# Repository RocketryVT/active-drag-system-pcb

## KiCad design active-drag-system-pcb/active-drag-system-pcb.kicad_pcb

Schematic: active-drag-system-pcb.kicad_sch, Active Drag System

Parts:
C1, C5: 0.1uF; C_0201_0603Metric_Pad0.64x0.40mm_HandSolder; Max Voltage 16 V; Tolerance 10%
C2, C3, C11, C12: 10uF; C_0805_2012Metric_Pad1.18x1.45mm_HandSolder; Max Voltage 16V; Tolerance 10%
C4: 1uF; C_0402_1005Metric_Pad0.74x0.62mm_HandSolder; Max Voltage 6.3V; Tolerance 20%
C6: 22p; C_0201_0603Metric; Max Voltage 25V; Tolerance 5%
C7, C8, C9, C10: 22uF; C_0402_1005Metric_Pad0.74x0.62mm_HandSolder; Max Voltage 10V; Tolerance 20%
C13, C16, C17, C18: 2.2u; C_0402_1005Metric_Pad0.74x0.62mm_HandSolder; Max Voltage 6.3V; Tolerance 20%
C14, C15, C19, C20, C21, C22, C23, C24, C27, C47, C48, C49, C50, C51, C53, C55, C56: 100n; C_0201_0603Metric_Pad0.64x0.40mm_HandSolder; Max Voltage 6.3V; Tolerance 10%
C25, C26: 15p; C_0201_0603Metric; Max Voltage 25V; Tolerance 5%
C46: 1000pF; C_0402_1005Metric_Pad0.74x0.62mm_HandSolder; Max Voltage 6.3V; Tolerance 10%
C52: 10n; C_0201_0603Metric_Pad0.64x0.40mm_HandSolder; Max Voltage 6.3V; Tolerance 10%
C54: 2.2u; C_0402_1005Metric_Pad0.74x0.62mm_HandSolder; Max Voltage 6.3V; Tolerance 10%
D7: WL-SMCW_0603
H1, H2, H3, H4: MountingHole; MountingHole_2.7mm_M2.5
IC1: ADC1283IPT; SOP65P640X120-16N; Manufacturer_Part_Number ADC1283IPT; Mouser Part Number 511-ADC1283IPT
J1: USB_B_Micro; USB_Micro-B_Amphenol_10103594-0001LF_Horizontal
L1: 104CDMCCDS-1R5MC; IND_-1R5MC_SUM
Q7: DMG1012T; SOT-523
R1, R2, R3: 100k; R_0402_1005Metric_Pad0.72x0.64mm_HandSolder; Tolerance 0.1%
R4: 200k; R_0402_1005Metric_Pad0.72x0.64mm_HandSolder; Tolerance 1%
R5: 150k; R_0402_1005Metric_Pad0.72x0.64mm_HandSolder; Tolerance 0.1%
R6, R8: 100k; R_0402_1005Metric_Pad0.72x0.64mm_HandSolder; Tolerance 1%
R7: 20k; R_0402_1005Metric_Pad0.72x0.64mm_HandSolder; Tolerance 0.1%
R9: 100; R_0402_1005Metric_Pad0.72x0.64mm_HandSolder; Tolerance 1%
R28, R29: 27; R_0201_0603Metric_Pad0.64x0.40mm_HandSolder; Tolerance 1%
R30: 1; R_0402_1005Metric_Pad0.72x0.64mm_HandSolder; Tolerance 1%
R31: 200; R_0603_1608Metric_Pad0.98x0.95mm_HandSolder; Tolerance 1%
R32, R33: 1k; R_0402_1005Metric_Pad0.72x0.64mm_HandSolder; Tolerance 1%
R34, R35: 10k; R_0402_1005Metric_Pad0.72x0.64mm_HandSolder; Tolerance 1%
SW1: PTS815 SJM 250 SMTR LFS; SW4_PTS815 SJM 250 SMTR LFS_CNK
U1: TPS51386RJNR; VREG_TPS51386RJNR; PARTREV *
U2: LD39200PU33R; SON_DFN6_3X3_STM
U3, U4: PMEG3050EP_115; SODFL4725X110N
U5: RP2040; QFN-56-1EP_7x7mm_P0.4mm_EP3.2x3.2mm
U6: W25Q128JVS; SOIC-8_5.23x5.23mm_P1.27mm
U13: MS5611-01BA; LGA-8_3x5mm_P1.25mm
U14: LSM6DSV16XTR; LGA14L_LSM6_STM
U15: ADXL375BCCZ; LGA_CC-14-1_ADI
U16: IIM-42653; PQFN50P250X300X97-14N; PARTREV 1.1
X1: ABM8-272-T3; ABM8-272-T3_ABR

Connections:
+1V1: C15.1, C17.1, C22.1, U5.23 (DVDD), U5.45 (VREG_VOUT), U5.50 (DVDD)
+3V3: C12.1, C13.1, C14.1, C16.1, C19.1, C20.1, C21.1, C23.1, C24.1, C27.1, C47.1, C48.1, C49.1, C50.1, C51.1, C52.1, C53.1, C54.1, C55.1, C56.1, IC1.2 (AVCC), IC1.13 (DVCC), Q7.1 (G), R31.1, R34.1, R35.1, U2.1 (OUT), U2.2 (ADJ/SENSE), U5.1 (IOVDD), U5.10 (IOVDD), U5.22 (IOVDD), U5.33 (IOVDD), U5.42 (IOVDD), U5.44 (VREG_IN), U5.48 (USB_VDD), U5.49 (IOVDD), U6.8 (VCC), U13.1 (VDD), U13.2 (PS), U14.5 (VDD_IO), U14.8 (VDD), U14.12 (CS), U15.1 (VDD_I/O), U15.6 (VS), U15.7 (*CS), U15.12 (SDO/ALT_ADDRESS), U16.5 (VDDIO), U16.8 (VDD), U16.12 (AP_CS); also elsewhere on the board
+5V: C6.2, C7.1, C8.1, C9.1, C10.1, L1.1, R5.2, U4.2 (A)
+BATT: C1.1, C2.1, C3.1, J1.1, R1.1, U1.1 (VIN); also elsewhere on the board
-BATT: C1.2, C2.2, C3.2, C4.2, C7.2, C8.2, C9.2, C10.2, C11.2, C12.2, C13.2, C14.2, C15.2, C16.2, C17.2, C18.2, C19.2, C20.2, C21.2, C22.2, C23.2, C24.2, C25.2, C26.2, C27.2, C46.2, C47.2, C48.2, C49.2, C50.2, C51.2, C52.2, C53.2, C54.2, C55.2, C56.2, D7.1, IC1.3 (AGND), IC1.12 (DGND), J1.2, R2.1, R6.2, R7.1, SW1.3, SW1.4, U1.2 (PGND), U1.10 (AGND), U2.3 (GND), U2.7 (GND), U5.19 (TESTEN), U5.57 (GND), U6.4 (GND), U13.3 (GND), U13.4 (CSB), U13.5 (CSB), U14.1 (SDO/SA0), U14.2 (SDx/AH1/QVAR1), U14.3 (SCx/AH2/QVAR2), U14.6 (GND), U14.7 (GND), U15.2 (GND), U15.3 (RESERVED), U15.4 (GND), U15.5 (GND), U15.11 (RESERVED), U16.1 (AP_SDO/AP_AD0), U16.6 (GND), U16.7 (RESV), X1.2, X1.4; also elsewhere on the board
/ADC_VREF: R30.1, R31.2
/GPIO6: U5.8 (GPIO6)
/GPIO8: U5.11 (GPIO8)
/GPIO10: U5.13 (GPIO10)
/GPIO16: U5.27 (GPIO16)
/GPIO17: U5.28 (GPIO17)
/GPIO22: U5.34 (GPIO22)
/GPIO24: U5.36 (GPIO24)
/GPIO25: R9.1, U5.37 (GPIO25)
/GPIO26_ADC0: U5.38 (GPIO26_ADC0)
/GPIO27_ADC1: U5.39 (GPIO27_ADC1)
/GPIO28_ADC2: U5.40 (GPIO28_ADC2)
/GPIO29_ADC3: Q7.2 (S), U5.41 (GPIO29_ADC3)
/HALL_A: U5.2 (GPIO0)
/HALL_B: U5.4 (GPIO2)
/HALL_C: U5.6 (GPIO4)
/HIGHG_INT1: U15.8 (INT1)
/HIGHG_INT2: U15.9 (INT2)
/HIN_A: U5.3 (GPIO1)
/HIN_B: U5.5 (GPIO3)
/HIN_C: U5.7 (GPIO5)
/I2C0_SCL: R34.2, U5.32 (GPIO21), U13.8 (SCLK), U14.13 (SCL), U15.14 (SCL/SCLK), U16.13 (AP_SCL/AP_SCLK)
/I2C0_SDA: R35.2, U5.31 (GPIO20), U13.7 (SDI/SDA), U14.14 (SDA), U15.13 (SDA/SDI/SDIO), U16.14 (AP_SDA/AP_SDIO/AP_SDI)
/I2C1_SCL: U5.30 (GPIO19)
/I2C1_SDA: U5.29 (GPIO18)
/LOWG_INT1: U14.4 (INT1), U14.9 (INT2)
/MIDG_INT1: U16.4 (INT1/INT)
/NLIN_A: U5.9 (GPIO7)
/NLIN_B: U5.12 (GPIO9)
/NLIN_C: U5.14 (GPIO11)
/QSPI_SCLK: U5.52 (QSPI_SCLK), U6.6 (CLK)
/QSPI_SD0: U5.53 (QSPI_SD0), U6.5 (DI(IO0))
/QSPI_SD1: U5.55 (QSPI_SD1), U6.2 (DO(IO1))
/QSPI_SD2: U5.54 (QSPI_SD2), U6.3 (IO2)
/QSPI_SD3: U5.51 (QSPI_SD3), U6.7 (IO3)
/QSPI_SS: R33.2, U5.56 (QSPI_SS), U6.1 (~CS)
/RP2040_CLKOUT1: U5.35 (GPIO23), U16.9 (INT2/FSYNC/CLKIN)
/RUN: U5.26 (RUN)
/SPI1_CSn: IC1.1 (~CS), U5.16 (GPIO13)
/SPI1_RX: IC1.15 (DOUT), U5.15 (GPIO12)
/SPI1_SCK: IC1.16 (SCLK), U5.17 (GPIO14)
/SPI1_TX: IC1.14 (DIN), U5.18 (GPIO15)
/SWCLK: U5.24 (SWCLK)
/SWD: U5.25 (SWD)
/USB_D+: R28.1; also elsewhere on the board
/USB_D-: R29.1; also elsewhere on the board
/VSYS: C11.1, R4.1, R8.1, U2.6 (IN), U3.1 (K), U4.1 (K)
/XIN: C26.1, U5.20 (XIN), X1.1
/XOUT: R32.1, U5.21 (XOUT)
CURRENT_SENSE_A: IC1.4 (IN0); also elsewhere on the board
CURRENT_SENSE_B: IC1.6 (IN2); also elsewhere on the board
CURRENT_SENSE_C: IC1.9 (IN5); also elsewhere on the board
unnamed: C25.1, R32.2, X1.3
unnamed: D7.2, R9.2
unnamed: C46.1, Q7.3 (D), R4.2, R6.1
unnamed: R33.1, SW1.1, SW1.2
unnamed: R1.2, R2.2, U1.11 (EN)
unnamed: C6.1, R5.1, R7.2, U1.4 (FB)
unnamed: R3.2, U1.3 (PG)
unnamed: C5.1, L1.2, U1.7 (SW)
unnamed: C5.2, U1.8 (VBST)
unnamed: C4.1, R3.1, U1.9 (VCC)
unnamed: R8.2, U2.5 (EN)
unnamed: C18.1, R30.2, U5.43 (ADC_AVDD)
unnamed: R29.2, U5.46 (USB_DM)
unnamed: R28.2, U5.47 (USB_DP)
VBUS: U3.2 (A); also elsewhere on the board
VOLTAGE_SENSE_A: IC1.5 (IN1); also elsewhere on the board
VOLTAGE_SENSE_B: IC1.7 (IN3); also elsewhere on the board
VOLTAGE_SENSE_C: IC1.10 (IN6); also elsewhere on the board

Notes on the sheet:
Power
Crystal
Motor Control
Sensors
Altimeter
Mid-G IMU
I2C0 Pullups
RP2040 (Primary MCU)
Low-G IMU
High-G IMU
12 MHz
Flash

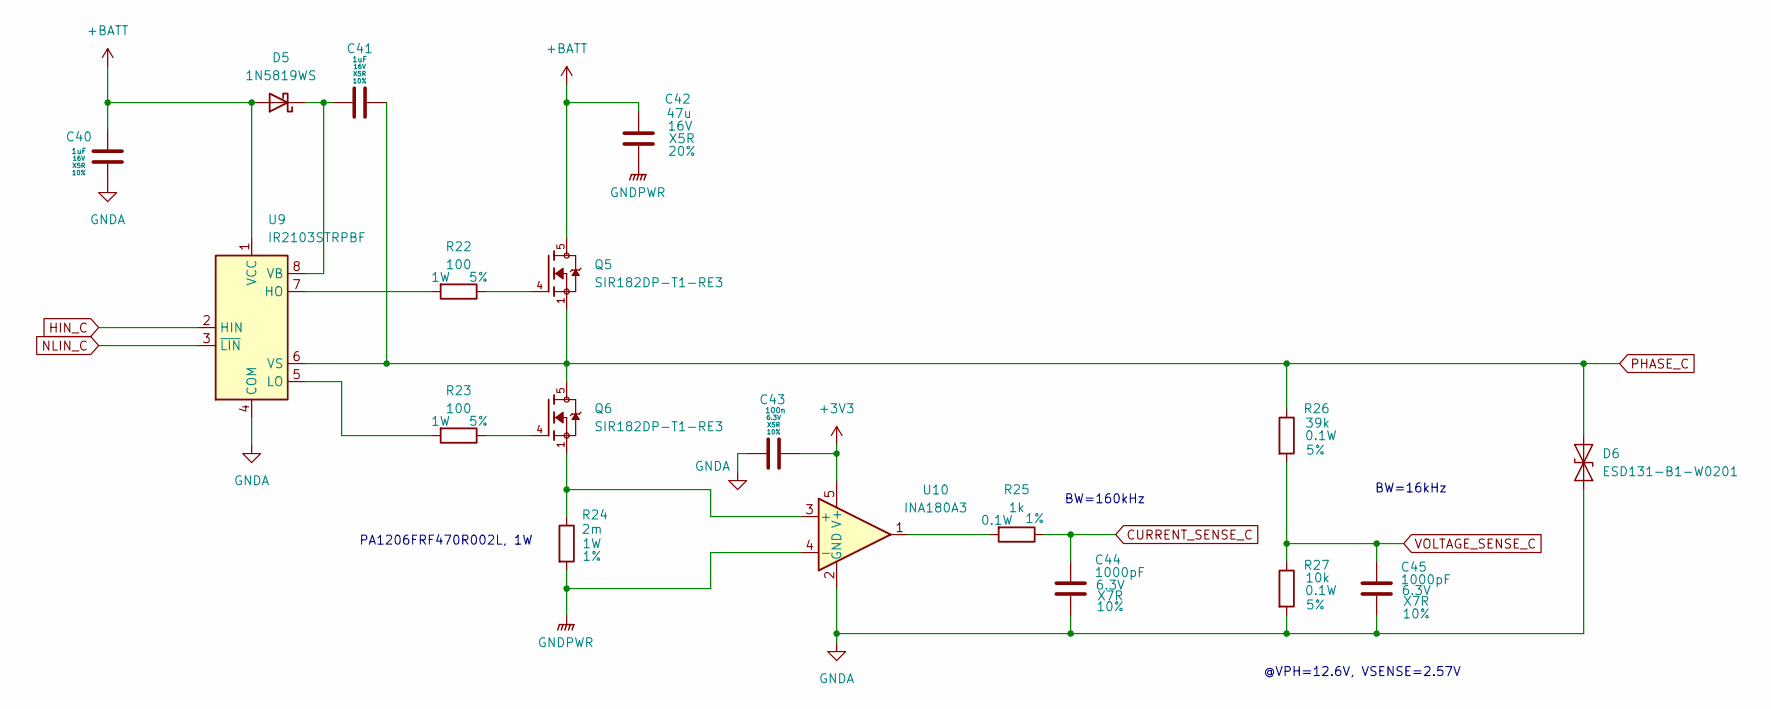
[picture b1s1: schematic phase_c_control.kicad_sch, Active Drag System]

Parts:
C40, C41: 1uF; C_0402_1005Metric_Pad0.74x0.62mm_HandSolder; Max Voltage 16V; Tolerance 10%
C42: 47u; C_1210_3225Metric_Pad1.33x2.70mm_HandSolder; Max Voltage 16V; Tolerance 20%
C43: 100n; C_0201_0603Metric_Pad0.64x0.40mm_HandSolder; Max Voltage 6.3V; Tolerance 10%
C44, C45: 1000pF; C_0402_1005Metric_Pad0.74x0.62mm_HandSolder; Max Voltage 6.3V; Tolerance 10%
D5: 1N5819WS; D_SOD-323
D6: ESD131-B1-W0201; Infineon_SG-WLL-2-3_0.58x0.28_P0.36mm
Q5, Q6: SIR182DP-T1-RE3; TRANS_SIR182DP-T1-RE3; PARTREV B
R22, R23: 100; R_2512_6332Metric_Pad1.40x3.35mm_HandSolder; Tolerance 5%
R24: 2m; R_1206_3216Metric_Pad1.30x1.75mm_HandSolder; Tolerance 1%
R25: 1k; R_0402_1005Metric_Pad0.72x0.64mm_HandSolder; Tolerance 1%
R26: 39k; R_0402_1005Metric_Pad0.72x0.64mm_HandSolder; Tolerance 5%
R27: 10k; R_0402_1005Metric_Pad0.72x0.64mm_HandSolder; Tolerance 5%
U9: IR2103STRPBF; SO8N_INF-L
U10: INA180A3; SOT-23-5

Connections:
+3V3: C43.2, U10.5 (V+); also elsewhere on the board
+BATT: C40.1, C42.1, D5.2 (A), Q5.5, U9.1 (VCC); also elsewhere on the board
-BATT: C40.2, C42.2, C43.1, C44.2, C45.2, D6.1 (A1), R24.2, R27.2, U9.4 (COM), U10.2 (GND), U10.4 (-); also elsewhere on the board
CURRENT_SENSE_C: C44.1, R25.1; also elsewhere on the board
HIN_C: U9.2 (HIN)
NLIN_C: U9.3 (~LIN)
unnamed: C41.2, D5.1 (K), U9.8 (VB)
unnamed: Q5.4, R22.1
unnamed: Q6.4, R23.1
unnamed: R25.2, U10.1
unnamed: R22.2, U9.7 (HO)
unnamed: R23.2, U9.5 (LO)
unnamed: Q6.1, R24.1, U10.3 (+)
PHASE_C: C41.1, D6.2 (A2), Q5.1, Q6.5, R26.1, U9.6 (VS)
VOLTAGE_SENSE_C: C45.1, R26.2, R27.1; also elsewhere on the board

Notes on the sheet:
PA1206FRF470R002L, 1W
BW=16kHz
BW=160kHz
@VPH=12.6V, VSENSE=2.57V

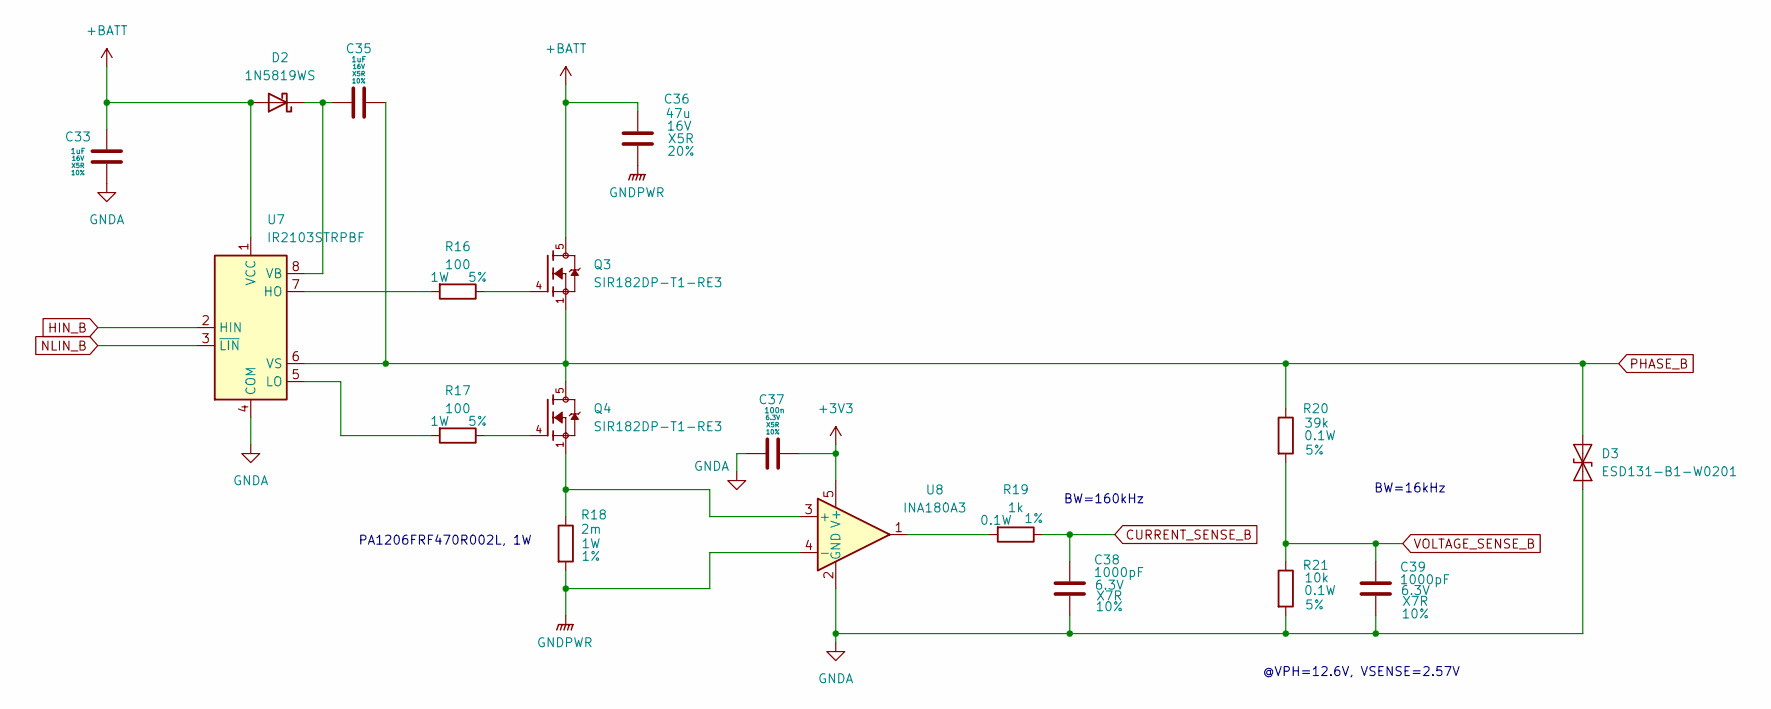
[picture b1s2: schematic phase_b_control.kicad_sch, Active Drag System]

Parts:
C33, C35: 1uF; C_0402_1005Metric_Pad0.74x0.62mm_HandSolder; Max Voltage 16V; Tolerance 10%
C36: 47u; C_1210_3225Metric_Pad1.33x2.70mm_HandSolder; Max Voltage 16V; Tolerance 20%
C37: 100n; C_0201_0603Metric_Pad0.64x0.40mm_HandSolder; Max Voltage 6.3V; Tolerance 10%
C38, C39: 1000pF; C_0402_1005Metric_Pad0.74x0.62mm_HandSolder; Max Voltage 6.3V; Tolerance 10%
D2: 1N5819WS; D_SOD-323
D3: ESD131-B1-W0201; Infineon_SG-WLL-2-3_0.58x0.28_P0.36mm
Q3, Q4: SIR182DP-T1-RE3; TRANS_SIR182DP-T1-RE3; PARTREV B
R16, R17: 100; R_2512_6332Metric_Pad1.40x3.35mm_HandSolder; Tolerance 5%
R18: 2m; R_1206_3216Metric_Pad1.30x1.75mm_HandSolder; Tolerance 1%
R19: 1k; R_0402_1005Metric_Pad0.72x0.64mm_HandSolder; Tolerance 1%
R20: 39k; R_0402_1005Metric_Pad0.72x0.64mm_HandSolder; Tolerance 5%
R21: 10k; R_0402_1005Metric_Pad0.72x0.64mm_HandSolder; Tolerance 5%
U7: IR2103STRPBF; SO8N_INF-L
U8: INA180A3; SOT-23-5

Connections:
+3V3: C37.2, U8.5 (V+); also elsewhere on the board
+BATT: C33.1, C36.1, D2.2 (A), Q3.5, U7.1 (VCC); also elsewhere on the board
-BATT: C33.2, C36.2, C37.1, C38.2, C39.2, D3.1 (A1), R18.2, R21.2, U7.4 (COM), U8.2 (GND), U8.4 (-); also elsewhere on the board
CURRENT_SENSE_B: C38.1, R19.1; also elsewhere on the board
HIN_B: U7.2 (HIN)
NLIN_B: U7.3 (~LIN)
unnamed: C35.2, D2.1 (K), U7.8 (VB)
unnamed: Q3.4, R16.1
unnamed: Q4.4, R17.1
unnamed: R19.2, U8.1
unnamed: R16.2, U7.7 (HO)
unnamed: R17.2, U7.5 (LO)
unnamed: Q4.1, R18.1, U8.3 (+)
PHASE_B: C35.1, D3.2 (A2), Q3.1, Q4.5, R20.1, U7.6 (VS)
VOLTAGE_SENSE_B: C39.1, R20.2, R21.1; also elsewhere on the board

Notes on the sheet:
PA1206FRF470R002L, 1W
BW=16kHz
BW=160kHz
@VPH=12.6V, VSENSE=2.57V

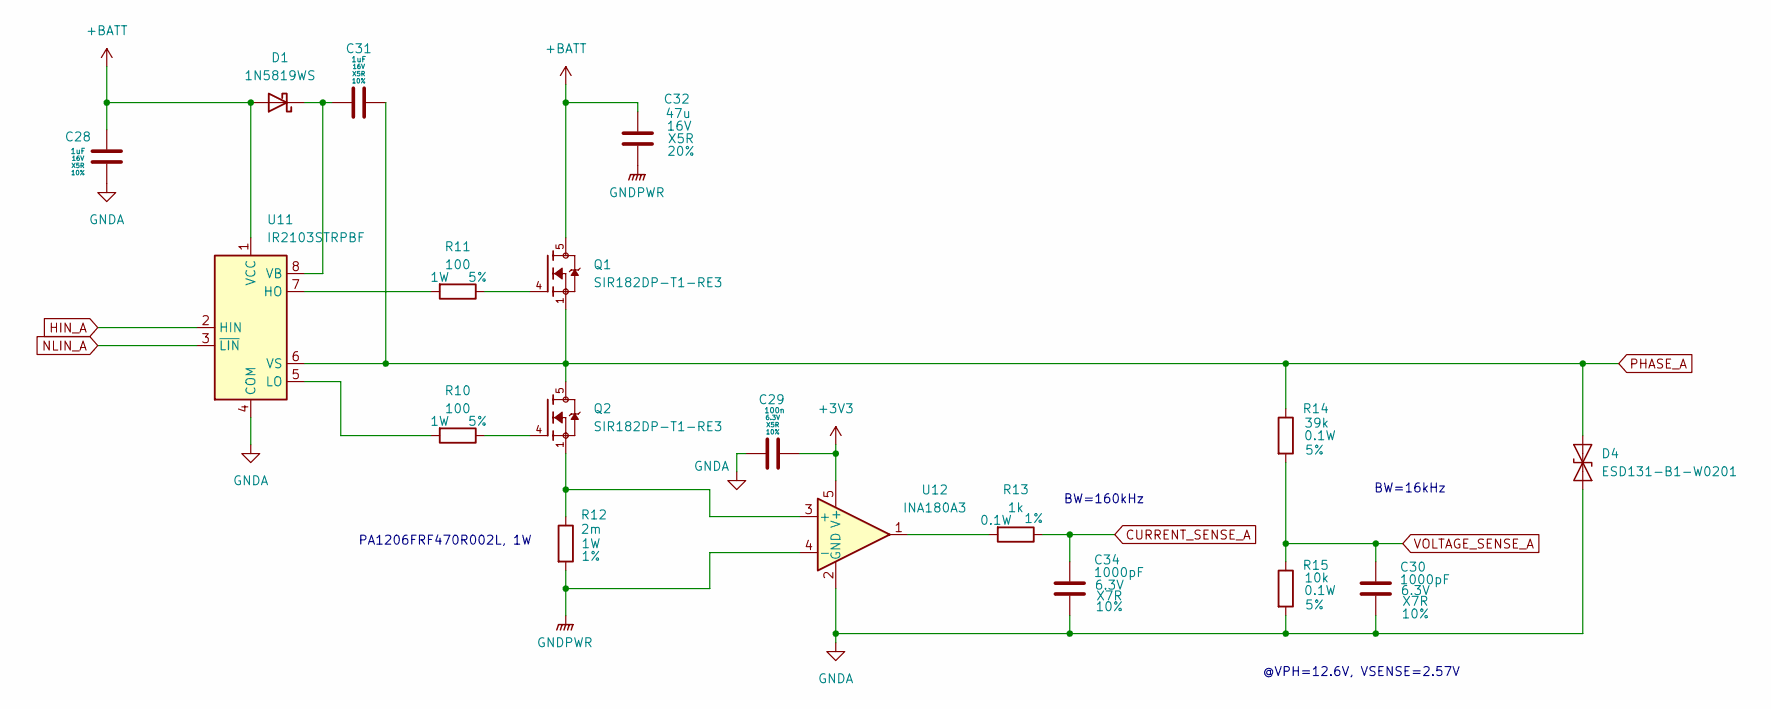
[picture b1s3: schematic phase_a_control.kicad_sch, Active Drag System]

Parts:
C28, C31: 1uF; C_0402_1005Metric_Pad0.74x0.62mm_HandSolder; Max Voltage 16V; Tolerance 10%
C29: 100n; C_0201_0603Metric_Pad0.64x0.40mm_HandSolder; Max Voltage 6.3V; Tolerance 10%
C30, C34: 1000pF; C_0402_1005Metric_Pad0.74x0.62mm_HandSolder; Max Voltage 6.3V; Tolerance 10%
C32: 47u; C_1210_3225Metric_Pad1.33x2.70mm_HandSolder; Max Voltage 16V; Tolerance 20%
D1: 1N5819WS; D_SOD-323
D4: ESD131-B1-W0201; Infineon_SG-WLL-2-3_0.58x0.28_P0.36mm
Q1, Q2: SIR182DP-T1-RE3; TRANS_SIR182DP-T1-RE3; PARTREV B
R10, R11: 100; R_2512_6332Metric_Pad1.40x3.35mm_HandSolder; Tolerance 5%
R12: 2m; R_1206_3216Metric_Pad1.30x1.75mm_HandSolder; Tolerance 1%
R13: 1k; R_0402_1005Metric_Pad0.72x0.64mm_HandSolder; Tolerance 1%
R14: 39k; R_0402_1005Metric_Pad0.72x0.64mm_HandSolder; Tolerance 5%
R15: 10k; R_0402_1005Metric_Pad0.72x0.64mm_HandSolder; Tolerance 5%
U11: IR2103STRPBF; SO8N_INF-L
U12: INA180A3; SOT-23-5

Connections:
+3V3: C29.2, U12.5 (V+); also elsewhere on the board
+BATT: C28.1, C32.1, D1.2 (A), Q1.5, U11.1 (VCC); also elsewhere on the board
-BATT: C28.2, C29.1, C30.2, C32.2, C34.2, D4.1 (A1), R12.2, R15.2, U11.4 (COM), U12.2 (GND), U12.4 (-); also elsewhere on the board
CURRENT_SENSE_A: C34.1, R13.1; also elsewhere on the board
HIN_A: U11.2 (HIN)
NLIN_A: U11.3 (~LIN)
unnamed: C31.2, D1.1 (K), U11.8 (VB)
unnamed: Q1.4, R11.1
unnamed: Q2.4, R10.1
unnamed: R13.2, U12.1
unnamed: R11.2, U11.7 (HO)
unnamed: R10.2, U11.5 (LO)
unnamed: Q2.1, R12.1, U12.3 (+)
PHASE_A: C31.1, D4.2 (A2), Q1.1, Q2.5, R14.1, U11.6 (VS)
VOLTAGE_SENSE_A: C30.1, R14.2, R15.1; also elsewhere on the board

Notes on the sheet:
PA1206FRF470R002L, 1W
BW=16kHz
BW=160kHz
@VPH=12.6V, VSENSE=2.57V

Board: 2 copper layers, 130 parts (0 on the bottom side), 73 nets, no tracks yet.

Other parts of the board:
J0: USB_B_Micro; USB_Micro-B_Amphenol_10103594-0001LF_Horizontal

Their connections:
/USB_D+: J0.3 (D+); also elsewhere on the board
/USB_D-: J0.2 (D-); also elsewhere on the board
GND: J0.5 (GND), J0.6 (Shield)
VBUS: J0.1 (VBUS); also elsewhere on the board

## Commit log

2024-09-22 Created Project
2024-09-29 Imported Minimal Design and some Symbols/Footprints
    We now have symbols for:
    -5v LDO
    -bluetooth
    -all three imu's
2024-10-06 Preliminary work connecting comms pins
    Work from about a week ago, was put on hiatus so I could research the more finnicky things with sensor comms (and ask Kemper questions about KiCad usage)
2024-10-06 3.3v ldo and 5v+8.4v switching schematic
2024-10-06 fixed power nets
2024-10-10 First Phase Motor Control
2024-10-12 Add other two phases; remove CYW43 for scope reasons
2024-10-13 Swapped out regulators for higher current output; removed 8.4 V regulator; now two grounds (power and analog)
2024-10-13 Copy pasting Pico Schematic
2024-10-14 Literally everything has footprints and is pretty connected together on schematic except for IIM
2024-10-14 Populated IIM-42653
2024-10-17 Footprints for IIM; Disconnect AUX1 from GND, Leave as No-Connect
2024-10-20 resizing schematic
2024-10-24 Updated Footprint library; Started component placement for 5V regulator
